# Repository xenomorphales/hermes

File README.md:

# Hermes

Hermes is a rolling base board that drives motors and gets feedback from encoders, IR distance sensors and limit switches.

Warning: before opening any file from this KiCad project, make sure to have a path set in KiCad (Preferences > Configure Paths) named XENOCAD and pointing to the KiCad subdirectory of our [xenocad repository](https://github.com/xenomorphales/xenocad).

[Back to our main project](https://github.com/xenomorphales/xenomorphales)

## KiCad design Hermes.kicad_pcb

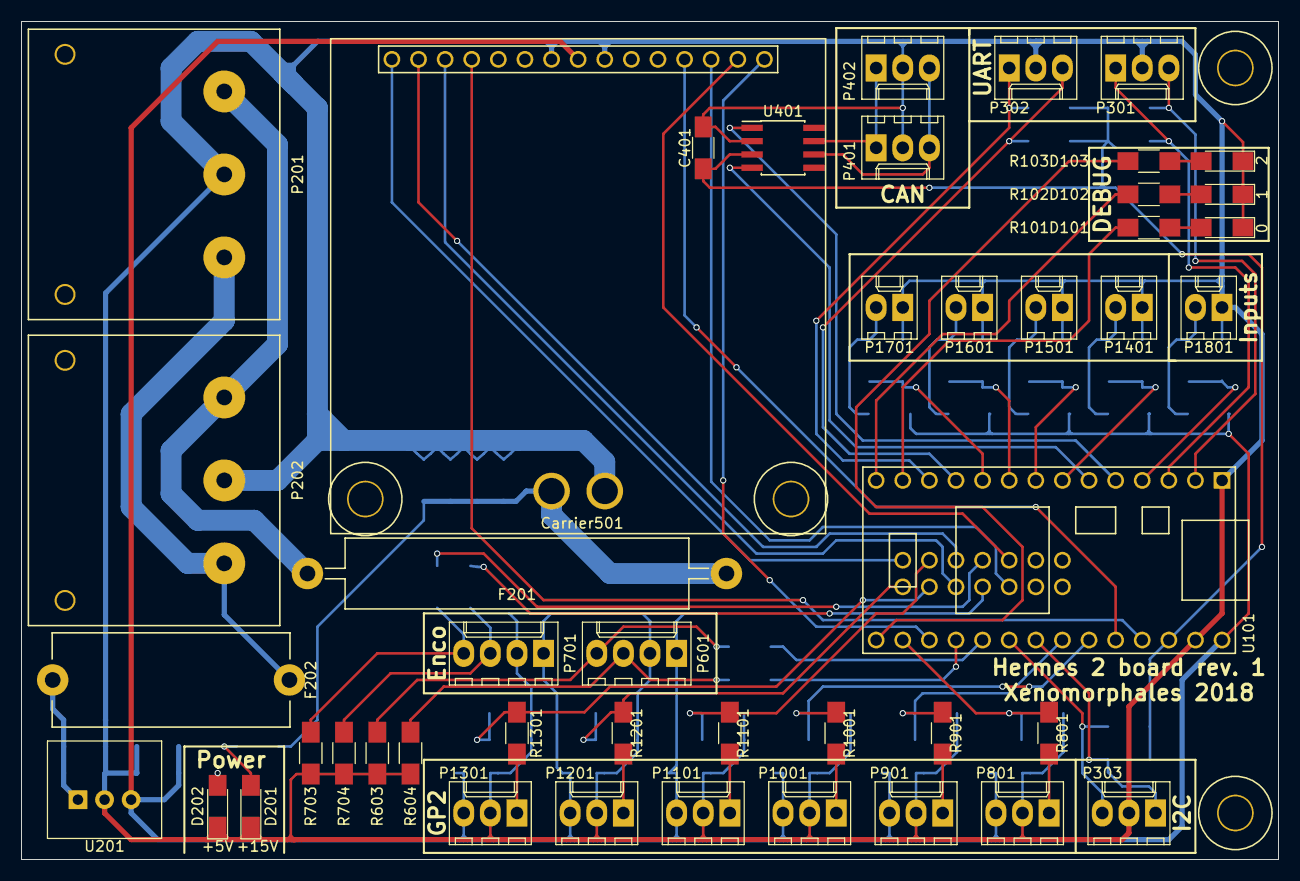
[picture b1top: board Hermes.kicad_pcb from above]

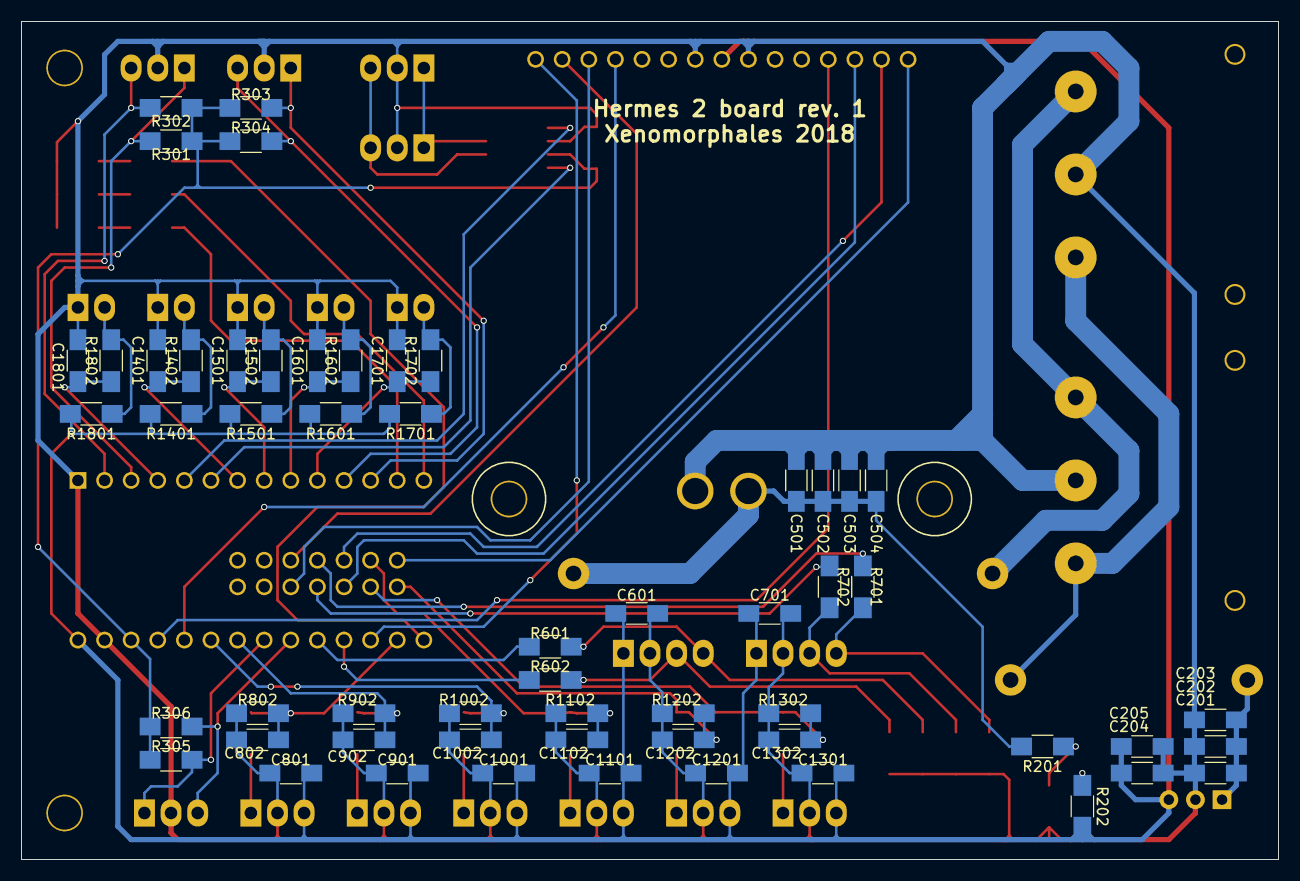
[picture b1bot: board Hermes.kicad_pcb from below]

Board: 2 copper layers, 120.0 x 80.0 mm, 101 parts (56 on the bottom side), 63 nets.

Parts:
C201, C501, C503, C801, C901, C1001, C1101, C1201, C1301: 10µF; C_1206_HandSoldering
C202, C203, C205, C401, C502, C504, C601, C701, C802, C902, C1002, C1102, C1202, C1302: 100nF; C_1206_HandSoldering
C204, C1401, C1501, C1601, C1701, C1801: 1µF; C_1206_HandSoldering
Carrier501: Pololu_Dual_VNHxSP30_Motor_Driver_Carrier; Pololu_Dual_VNHxSP30_Motor_Driver_no_output
D101, D102, D103: LED_Debug; LED_1206_HandSoldering
D201: LED_15V; LED_1206_HandSoldering
D202: LED_5V; LED_1206_HandSoldering
F201: FUSE 30A; Fuse_Eaton-ABC_20A+_Axial
F202: FUSE 1A; Fuseholder_Littlefuse-646
P201, P202: Power_IO; Hirose_DF22-03P-7.92DS_03x7.92mm_Angled
P301, P302: UART_IO; Molex_KK-6410-03_03x2.54mm_Straight
P303: I2C_IO; Molex_KK-6410-03_03x2.54mm_Straight
P401, P402: CAN_IO; Molex_KK-6410-03_03x2.54mm_Straight
P601, P701: Encoder_IO; Molex_KK-6410-04_04x2.54mm_Straight
P801, P901, P1001, P1101, P1201, P1301: GP2_IO; Molex_KK-6410-03_03x2.54mm_Straight
P1401, P1501, P1601, P1701, P1801: DebouncedInput_IO; Molex_KK-6410-02_02x2.54mm_Straight
R101, R102, R103: 120Ω; R_1206_HandSoldering
R201: 6kΩ; R_1206_HandSoldering
R202: 1.4kΩ; R_1206_HandSoldering
R301, R302, R303, R304, R603, R604, R703, R704, R801, R901, R1001, R1101, R1201, R1301: 10kΩ; R_1206_HandSoldering
R305, R306: 2kΩ; R_1206_HandSoldering
R601, R602, R701, R702: 22Ω; R_1206_HandSoldering
R802, R902, R1002, R1102, R1202, R1302: 20kΩ; R_1206_HandSoldering
R1401, R1501, R1601, R1701, R1801: 100kΩ; R_1206_HandSoldering
R1402, R1502, R1602, R1702, R1802: 18kΩ; R_1206_HandSoldering
U101: Teensy3.2; Teensy30_31_32_LC_sides_bottom
U201: OKI78SR5/1.5W36C; OKI-78SR-Vertical
U401: SN65HVD232; SOIC-8_3.9x4.9mm_Pitch1.27mm

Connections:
/+3.3V: C401.1, R301.1, R302.1, R303.1, R304.1, R305.1, R306.1, U101.31, U401.3
/+5V: C204.1, C205.1, C601.1, C701.1, C801.2, C901.2, C1001.2, C1101.2, C1201.2, C1301.2, Carrier501.8, P601.1, P701.1, P801.3, P901.3, P1001.3, P1101.3, P1201.3, P1301.3, R202.1, R1401.1, R1501.1, R1601.1, R1701.1, R1801.1, U101.33, U201.3
/+15V: C501.1, C502.1, C503.1, C504.1, Carrier501.19, F201.2, R201.1
/CAN_RX: U101.6, U401.4
/CAN_TX: U101.5, U401.1
/DIAG_1: Carrier501.1, U101.22
/DIAG_2: Carrier501.15, U101.44
/ENC_1_A: R602.1, U101.23
/ENC_1_B: R601.1, U101.24
/ENC_2_A: R702.1, U101.48
/ENC_2_B: R701.1, U101.41
/GND: C201.2, C202.2, C203.2, C204.2, C205.2, C401.2, C501.2, C502.2, C503.2, C504.2, C601.2, C701.2, C801.1, C802.1, C901.1, C902.1, C1001.1, C1002.1, C1101.1, C1102.1, C1201.1, C1202.1, C1301.1, C1302.1, C1401.2, C1501.2, C1601.2, C1701.2, C1801.2, Carrier501.7, Carrier501.9, Carrier501.18, D101.1, D102.1, D103.1, D201.1, D202.1, P201.2, P202.2, P301.2, P302.2, P303.2, P401.2, P402.2, P601.2, P701.2, P801.2, P901.2, P1001.2, P1101.2, P1201.2, P1301.2, P1401.1, P1501.1, P1601.1, P1701.1, P1801.1, R603.1, R604.1, R703.1, R704.1, R802.1, R902.1, R1002.1, R1102.1, R1202.1, R1302.1, U101.1, U101.32, U201.2, U401.2
/GP2_1_Signal: C802.2, R801.1, R802.2, U101.21
/GP2_2_Signal: C902.2, R901.1, R902.2, U101.27
/GP2_3_Signal: C1002.2, R1001.1, R1002.2, U101.28
/GP2_4_Signal: C1102.2, R1101.1, R1102.2, U101.43
/GP2_5_Signal: C1202.2, R1201.1, R1202.2, U101.45
/GP2_6_Signal: C1302.2, R1301.1, R1302.2, U101.46
/IN_A_1: Carrier501.2, U101.40
/IN_A_2: Carrier501.14, U101.42
/IN_B_1: Carrier501.3, U101.49
/IN_B_2: Carrier501.13, U101.47
/LED_Debug0: R101.1, U101.13
/LED_Debug1: R102.1, U101.14
/LED_Debug2: R103.1, U101.20
/LimitSwitch_1_Signal: C1401.1, R1402.1, U101.7
/LimitSwitch_2_Signal: C1501.1, R1502.1, U101.8
/LimitSwitch_3_Signal: C1601.1, R1602.1, U101.9
/LimitSwitch_4_Signal: C1701.1, R1702.1, U101.10
/PWM_1: Carrier501.4, U101.29
/PWM_2: Carrier501.12, U101.30
/PullSignal: C1801.1, R1802.1, U101.4
/SCL: P303.1, R305.2, U101.26
/SDA: P303.3, R306.2, U101.25
/UART0_RX: P301.3, R302.2, U101.2
/UART0_TX: P301.1, R301.2, U101.3
/UART1_RX: P302.3, R304.2, U101.11
/UART1_TX: P302.1, R303.2, U101.12
unnamed: C201.1, C202.1, C203.1, F202.2, U201.1
unnamed: D101.2, R101.2
unnamed: D102.2, R102.2
unnamed: D103.2, R103.2
unnamed: D201.2, R201.2
unnamed: D202.2, R202.2
unnamed: F201.1, P201.3, P202.3
unnamed: F202.1, P201.1, P202.1
unnamed: P401.1, P402.1, U401.7
unnamed: P401.3, P402.3, U401.6
unnamed: P601.3, R602.2, R604.2
unnamed: P601.4, R601.2, R603.2
unnamed: P701.3, R702.2, R704.2
unnamed: P701.4, R701.2, R703.2
unnamed: P801.1, R801.2
unnamed: P901.1, R901.2
unnamed: P1001.1, R1001.2
unnamed: P1101.1, R1101.2
unnamed: P1201.1, R1201.2
unnamed: P1301.1, R1301.2
unnamed: P1401.2, R1401.2, R1402.2
unnamed: P1501.2, R1501.2, R1502.2
unnamed: P1601.2, R1601.2, R1602.2
unnamed: P1701.2, R1701.2, R1702.2
unnamed: P1801.2, R1801.2, R1802.2

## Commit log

2017-11-11 First commit. Added LICENSE and README files.
2017-11-11 Adding Hermes 1 files.
2017-11-11 Adding Hermes 2 schematic files.
2017-11-18 Adding Hermes 2 specification file (first part).
2017-11-18 Moving the 5V regulator to the non-emergency-stop-guarded +15V and adding a fuse for it.
2017-12-22 Changing I2C pull-up resistors to 2kohm to allow I2C bus to work in fast-mode.
2017-12-22 Rearranging encoder sheet so GND is at the bottom and power supply at the top.
2017-12-22 Rewording debounced input sheet's comment.
2017-12-22 Changing some value fields on the schematics for a better grouped_csv BOM generation.
2017-12-22 Changing the LM7805 for a OKI78SR5/1.5W36C since it would heat way too much with a +15V input.
2017-12-23 Replacing the 5V regulator's input 220nF capacitor with two 100nF capacitors.
2017-12-23 Updating the schematic's annotations.
2017-12-31 Adding BOM.
    Just a few external components (like wires) are missing.
2018-01-01 Updating BOM.
    Still a few components are missing.
2018-01-13 Updating BOM.
    - Adding 14AWG power wires
    - Changing female power connector contact for 14AWG wires
2018-01-13 Setting the schematic's footprints.
2018-02-17 Fixing driver sheet after Pololu Dual VNHxSP30 Motor Driver schema update on xenocad.
2018-02-18 Adding the PCB layout.
2018-02-24 Updating BOM.
    Changing break away socket for the Teensy's underneath pins from 8 positions to 14.
